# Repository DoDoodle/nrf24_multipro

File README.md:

# nrf24-multipro
nRF24L01 multi-protocol RC transmitter

##!!!ATENTION

This work where based on Goebish´s work, and the main intention were make available for makers all over the world the pdb in eaglecad format

The folder pdb where added. If you have the ways to make it makeit.

[Need a module ?](mailto:goebish@gmail.com?Subject=nrf24-multipro%20module)

### Binding Procedure
- Create a model in OpenTX using external module in PPM mode, 12 channels and TAER sequence order.
- Turn off Taranis.
- Power up quad.
- While holding the appropriate stick pattern listed below, power up Taranis.
- Arm quad based on it's firmware's specification.

##### Protocol is selected with stick position at startup:

- Rudder right + Aileron right + Elevator down = EAchine E010, NiHui NH-010, JJRC H36 mini  
- Rudder right + Aileron right + Elevator up = FQ-777-124 Pocket Drone  
- Rudder right + Aileron left + Elevator up = CX-10 older red PCB/CX11/CX205/CX30, JXD389/391/393, SH6057/6043/6044/6046/6047, FY326Q7, WLToys v252 Pro/v343, XinXun X28/X30/X33/X39/X40   
- Rudder right + Aileron left + Elevator down = WLToys V930/931/939/966/977/988  
- Rudder right + Elevator down = HiSky RXs, HFP80, HCP80/100, FBL70/80/90/100, FF120, HMX120, WLToys v933/944/955  
- Rudder right + Elevator up = Syma X5C (older model), X2 ...  
- Rudder right + Aileron right = MJX X600  
- Rudder right + Aileron left = EAchine H8 mini 3D, JJRC H20/H22   
- Elevator down + Aileron left = Syma X5C-1/X11/X11C/X12  
- Elevator down + Aileron right = Attop YD-822/YD-829/YD-829C ...  
- Elevator up + Aileron right = EAchine H8(C) mini, BayangToys X6/X7/X9, JJRC JJ850, Floureon H101 ...  
- Elevator up + Aileron left = EAchine H7  
- Elevator up = WLToys V202/252/272, JXD 385/388, JJRC H6C, Yizhan Tarantula X6 ...  
- Elevator down = EAchine CG023/CG031/3D X4  
- Aileron left = Cheerson CX-10 green pcb  
- Aileron right = Cheerson CX-10 blue pcb & some newer red pcb, CX-10A, CX-10C, CX11, CX12, Floureon FX10, JJRC DHD D1  

Last used protocol is automatically selected if stick is in neutral position.

##### Extra features (if available on aircraft):

- Channel 5: led light, 3 pos. rate on CX-10 and FQ777-124, H7, inverted flight on H101  
- Channel 6: flip control  
- Channel 7: still camera  
- Channel 8: video camera, pitch trim (FQ777-124)  
- Channel 9: headless  
- Channel 10: calibrate Y (V2x2), pitch trim (H7), RTH (H8 mini/H20, FQ777-124), 360deg flip mode (H8 mini 3D/H22)  
- Channel 11: calibrate X (V2x2), roll trim (H7,FQ777-124)  
- Channel 12: Reset / Rebind

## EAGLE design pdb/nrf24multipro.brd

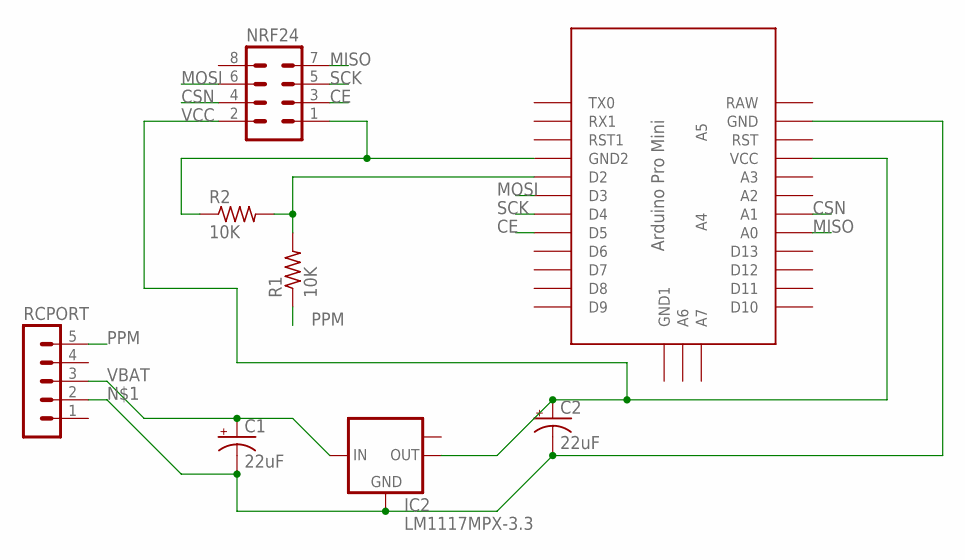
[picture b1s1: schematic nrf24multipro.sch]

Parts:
C1, C2: 22uF; E1,8-4
IC2: LM1117MPX-3.3; SOT223
NRF24: MA04-2
R1, R2: 10K; 0207/10
RCPORT: MA05-1
U$1: ABK-PRO-MINI

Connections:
CE: NRF24.3, U$1.D5
CSN: NRF24.4, U$1.A1
MISO: NRF24.7, U$1.A0
MOSI: NRF24.6, U$1.D3
unnamed: C1.-, C2.-, IC2.1 (GND), RCPORT.2, U$1.GND
unnamed: R1.2, R2.2, U$1.D2
unnamed: NRF24.1, R2.1, U$1.GND1 (GND2)
PPM: R1.1, RCPORT.5
SCK: NRF24.5, U$1.D4
VBAT: C1.+, IC2.3 (IN), RCPORT.3
VCC: C2.+, IC2.2 (OUT), NRF24.2, U$1.VCC

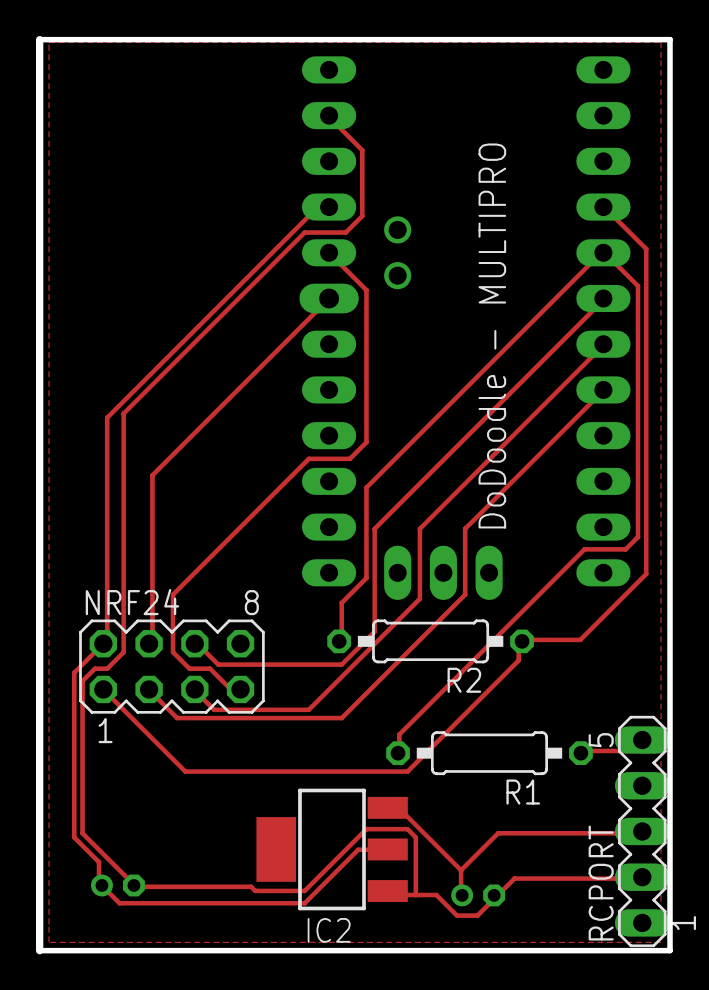
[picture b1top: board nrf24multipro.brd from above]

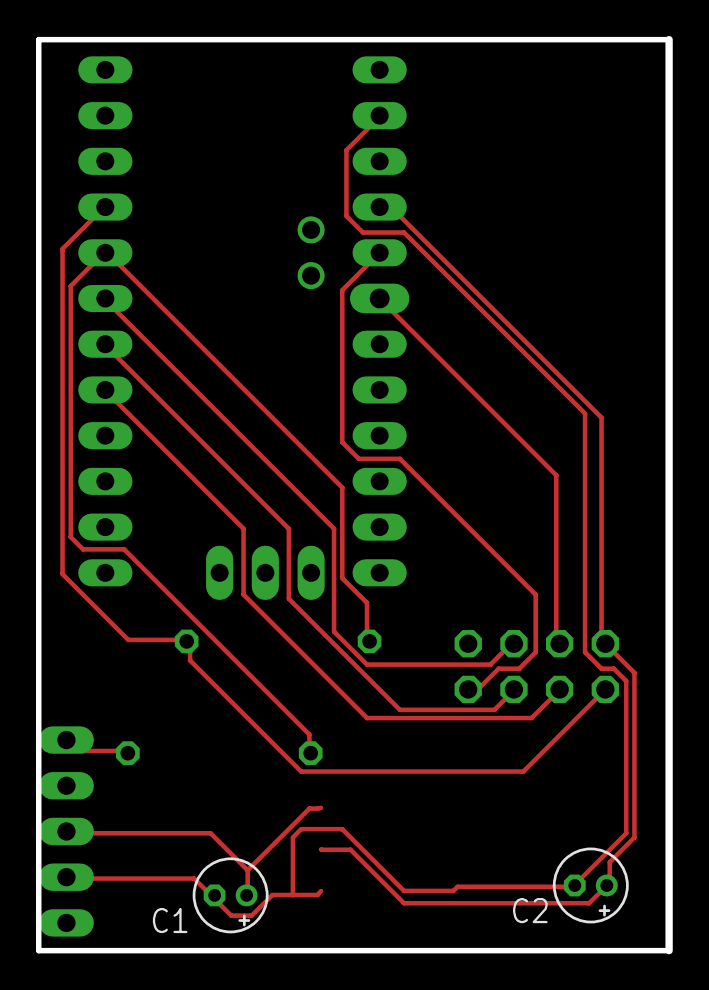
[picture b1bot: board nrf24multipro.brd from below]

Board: 2 copper layers, 35.0 x 50.6 mm, 8 parts (3 on the bottom side), 11 nets.

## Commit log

2017-04-06 with pdb
2017-04-22 added declaration in section attention.
2017-04-22 fixed error with .md
